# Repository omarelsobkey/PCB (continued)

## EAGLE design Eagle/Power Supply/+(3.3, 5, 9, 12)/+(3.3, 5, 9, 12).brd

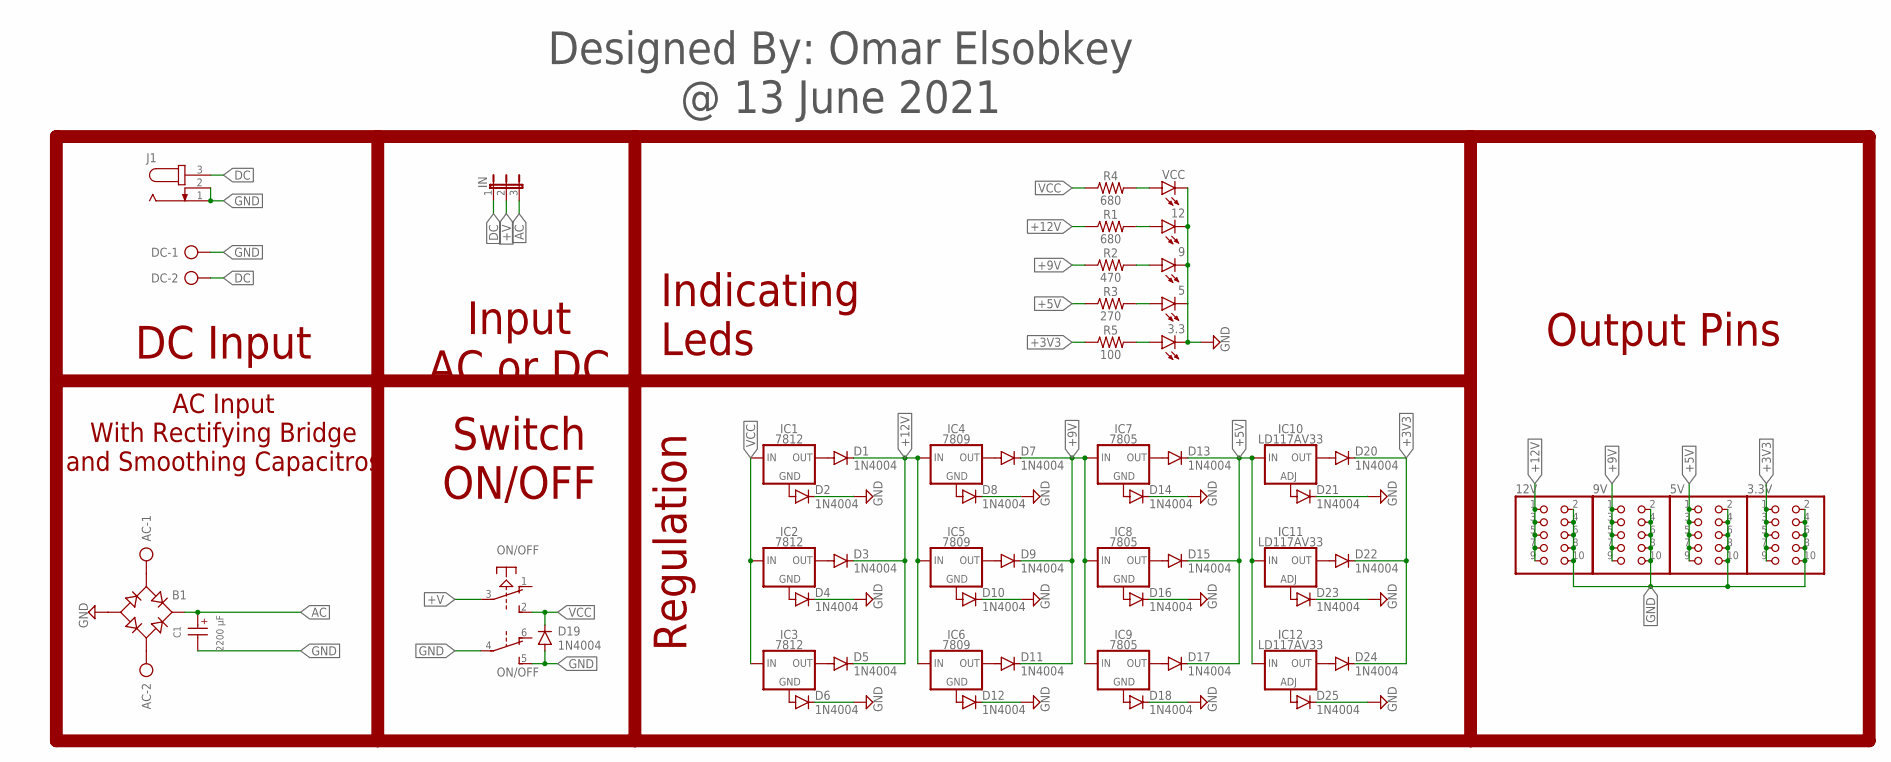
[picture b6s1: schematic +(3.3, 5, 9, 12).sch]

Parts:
3.3, 5, 9, 12: LED5MM
3.3V, 5V, 9V, 12V: PINHD-2X5; 2X05
AC: AK500/2-H
B1: RB1A
C1: 2200 µF; WCAP-ATG8_16X25(DXL)
D1, D2, D3, D4, D5, D6, D7, D8, D9, D10, D11, D12, D13, D14, D15, D16, D17, D18, D19, D20, D21, D22, D23, D24, D25: 1N4004; DO41-10
DC: AK500/2-H
IC1, IC2, IC3: 7812; 78XXS
IC4, IC5, IC6: 7809; 78XXS
IC7, IC8, IC9: 7805; 78XXS
IC10, IC11, IC12: LD117AV33; TO220L1
IN: JP2E; JP2
J1: JACK-PLUG0; SPC4077
ON/OFF: PVA2R
R1, R4: 680; AXIAL-0.3
R2: 470; AXIAL-0.3
R3: 270; AXIAL-0.3
R5: 100; AXIAL-0.3
VCC: LED5MM

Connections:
+3V3: 3.3V.1, 3.3V.3, 3.3V.5, 3.3V.7, 3.3V.9, D20.C, D22.C, D24.C, R5.P$1 (1)
+5V: 5V.1, 5V.3, 5V.5, 5V.7, 5V.9, D13.C, D15.C, D17.C, IC10.3 (IN), IC11.3 (IN), IC12.3 (IN), R3.P$1 (1)
+9V: 9V.1, 9V.3, 9V.5, 9V.7, 9V.9, D7.C, D9.C, D11.C, IC7.IN, IC8.IN, IC9.IN, R2.P$1 (1)
+12V: 12V.1, 12V.3, 12V.5, 12V.7, 12V.9, D1.C, D3.C, D5.C, IC4.IN, IC5.IN, IC6.IN, R1.P$1 (1)
+V: IN.2, ON/OFF.3
AC: B1.+, C1.1 (+), IN.3
DC: DC.2, IN.1, J1.3
GND: 3.3.K (C), 3.3V.2, 3.3V.4, 3.3V.6, 3.3V.8, 3.3V.10, 5.K (C), 5V.2, 5V.4, 5V.6, 5V.8, 5V.10, 9.K (C), 9V.2, 9V.4, 9V.6, 9V.8, 9V.10, 12.K (C), 12V.2, 12V.4, 12V.6, 12V.8, 12V.10, B1.-, C1.2 (-), D2.C, D4.C, D6.C, D8.C, D10.C, D12.C, D14.C, D16.C, D18.C, D19.A, D21.C, D23.C, D25.C, DC.1, J1.1, J1.2, ON/OFF.4, ON/OFF.5 (S), VCC.K (C)
unnamed: AC.1, B1.AC1
unnamed: AC.2, B1.AC2
unnamed: 3.3.A, R5.P$2 (2)
unnamed: R4.P$2 (2), VCC.A
unnamed: D21.A, IC10.1 (ADJ)
unnamed: D1.A, IC1.OUT
unnamed: D2.A, IC1.GND
unnamed: D3.A, IC2.OUT
unnamed: D4.A, IC2.GND
unnamed: D5.A, IC3.OUT
unnamed: D6.A, IC3.GND
unnamed: D7.A, IC4.OUT
unnamed: D8.A, IC4.GND
unnamed: D9.A, IC5.OUT
unnamed: D10.A, IC5.GND
unnamed: D11.A, IC6.OUT
unnamed: D12.A, IC6.GND
unnamed: D13.A, IC7.OUT
unnamed: D14.A, IC7.GND
unnamed: D15.A, IC8.OUT
unnamed: D16.A, IC8.GND
unnamed: D17.A, IC9.OUT
unnamed: D18.A, IC9.GND
unnamed: 12.A, R1.P$2 (2)
unnamed: 9.A, R2.P$2 (2)
unnamed: 5.A, R3.P$2 (2)
unnamed: D22.A, IC11.2 (OUT)
unnamed: D23.A, IC11.1 (ADJ)
unnamed: D24.A, IC12.2 (OUT)
unnamed: D25.A, IC12.1 (ADJ)
unnamed: D20.A, IC10.2 (OUT)
VCC: D19.C, IC1.IN, IC2.IN, IC3.IN, ON/OFF.2 (S), R4.P$1 (1)

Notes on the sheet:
Regulation
Indicating Leds
Input AC or DC
Switch ON/OFF
AC Input With Rectifying Bridge and Smoothing Capacitros
DC Input
Output Pins
Designed By: Omar Elsobkey @ 13 June 2021

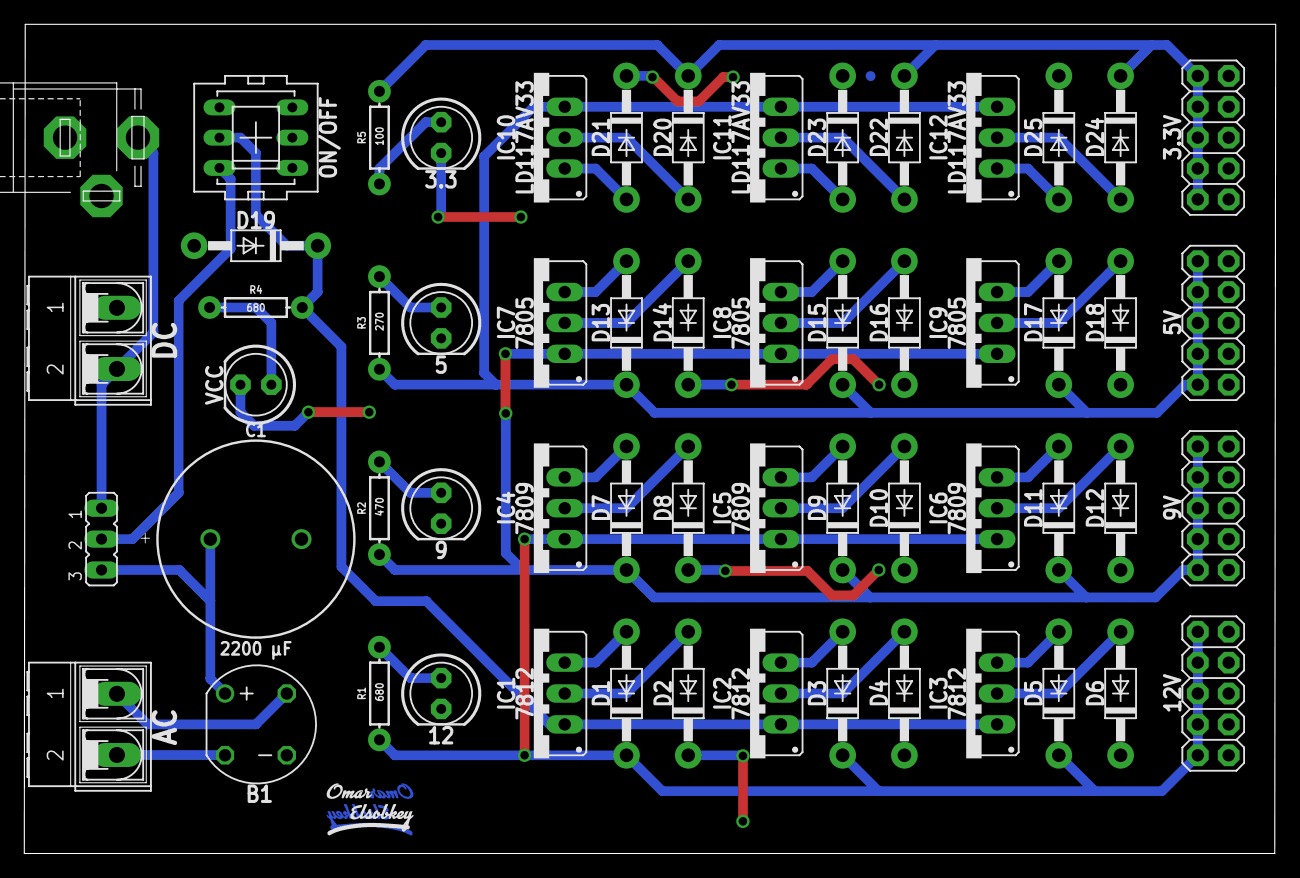
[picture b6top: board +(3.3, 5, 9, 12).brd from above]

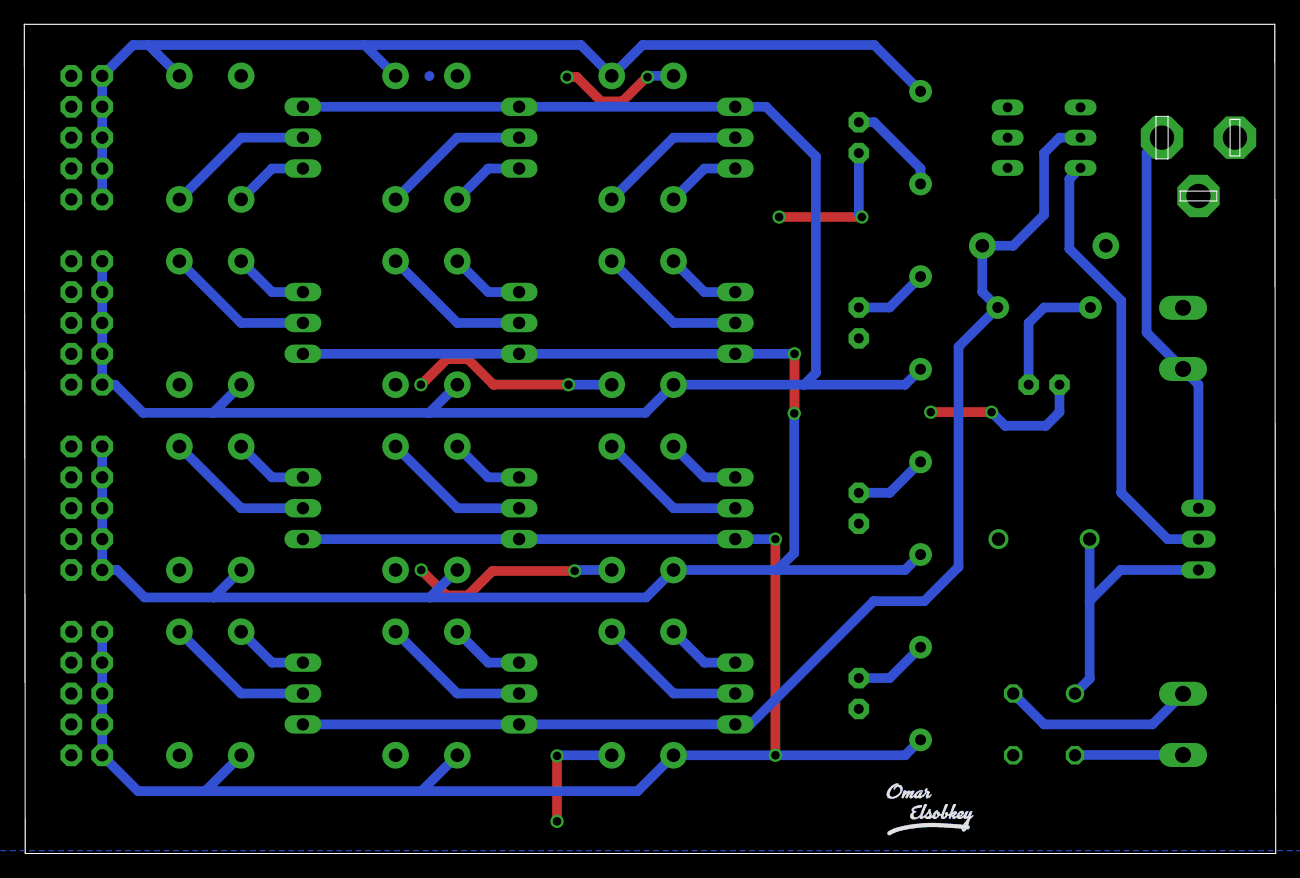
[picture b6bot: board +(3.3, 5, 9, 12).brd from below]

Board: 2 copper layers, 102.9 x 68.2 mm, 61 parts (2 on the bottom side), 40 nets.

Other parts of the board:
U$1: OMAR_ELSOBKEY_X0.5_T
U$2, U$3: OMAR_ELSOBKEY_X0.5_TN

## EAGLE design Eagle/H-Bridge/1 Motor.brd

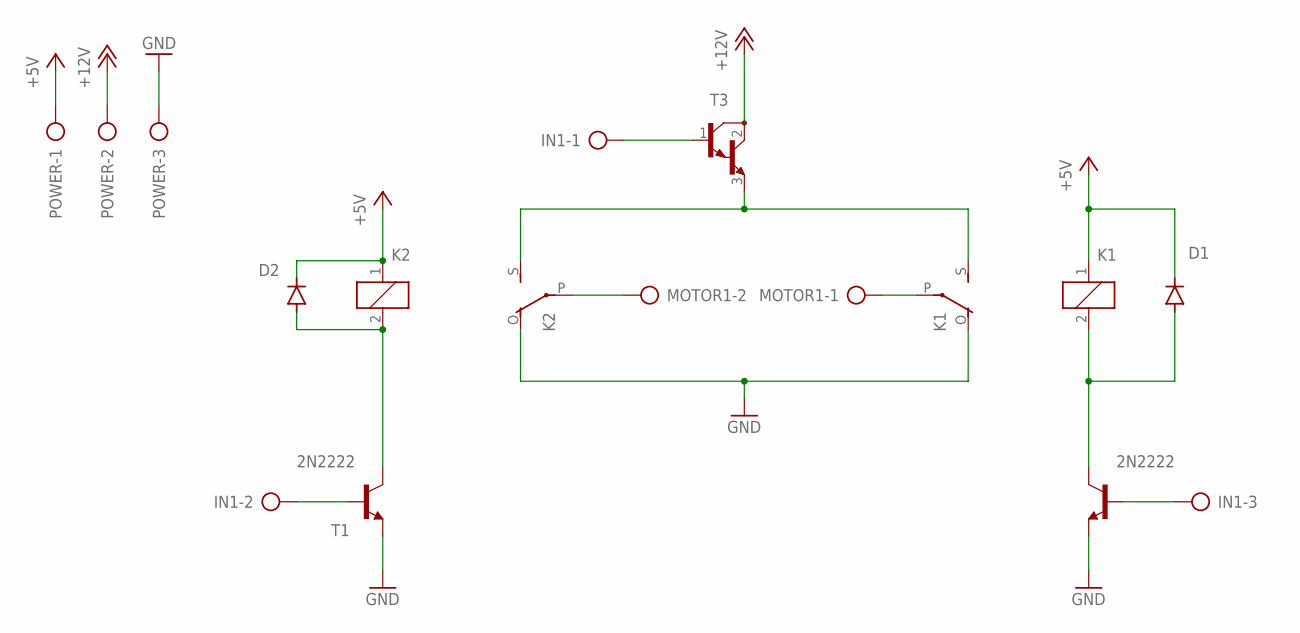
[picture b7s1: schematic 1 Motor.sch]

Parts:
D1, D2: 1N4004; DO41-10
IN1: AK300/3
K1, K2: ZF112
MOTOR1: AK300/2
POWER: AK300/3
T1, T2: 2N2222; TO92-EBC
T3: TIP122; TO220

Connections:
+5V: D1.C, D2.C, K1.1, K2.1, POWER.1
+12V: POWER.2, T3.2 (C)
EN: IN1.1, T3.1 (B)
GND: K1.O, K2.O, POWER.3, T1.E, T2.E
IN1: IN1.2, T1.B
IN2: IN1.3, T2.B
unnamed: K2.P, MOTOR1.2
unnamed: D1.A, K1.2, T2.C
unnamed: K1.P, MOTOR1.1
unnamed: D2.A, K2.2, T1.C
NO: K1.S, K2.S, T3.3 (E)

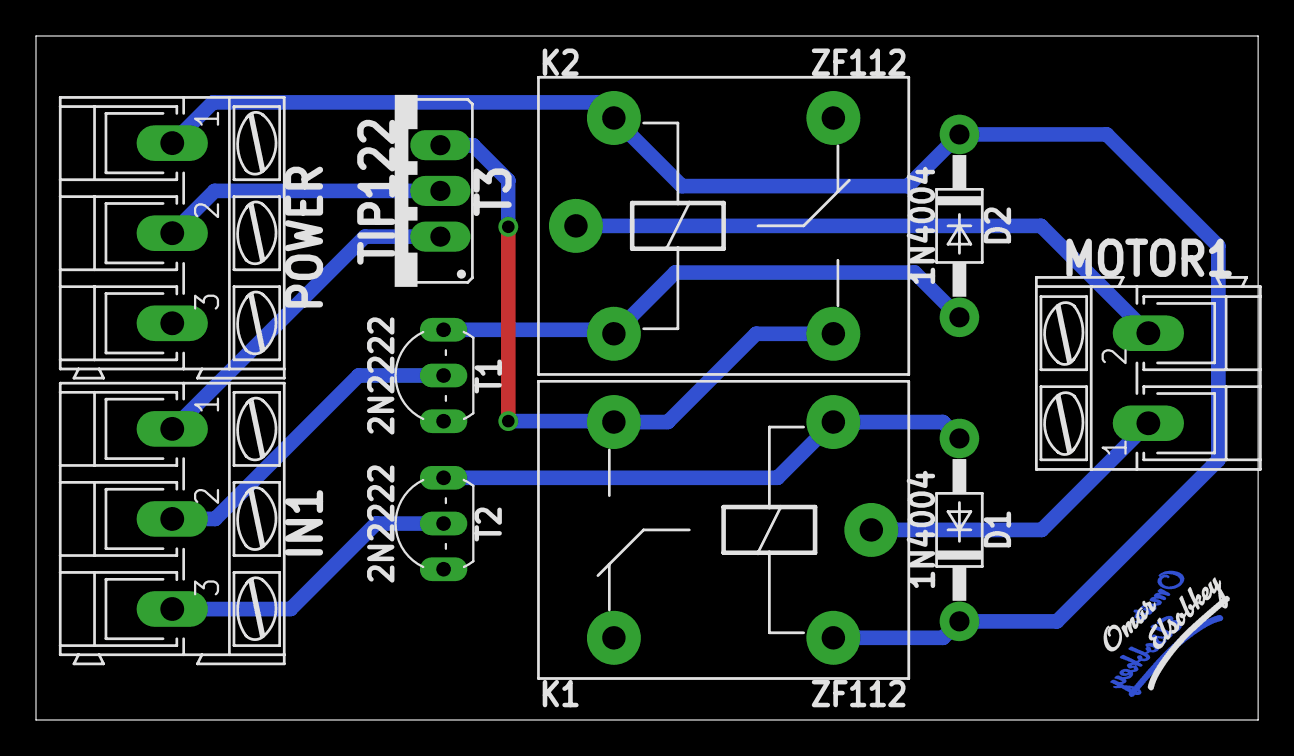
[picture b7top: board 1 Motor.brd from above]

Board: 2 copper layers, 67.9 x 38.0 mm, 12 parts (1 on the bottom side), 11 nets.

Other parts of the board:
U$1: OMAR_ELSOBKEY_X0.5_T
U$2: OMAR_ELSOBKEY_X0.5_TN

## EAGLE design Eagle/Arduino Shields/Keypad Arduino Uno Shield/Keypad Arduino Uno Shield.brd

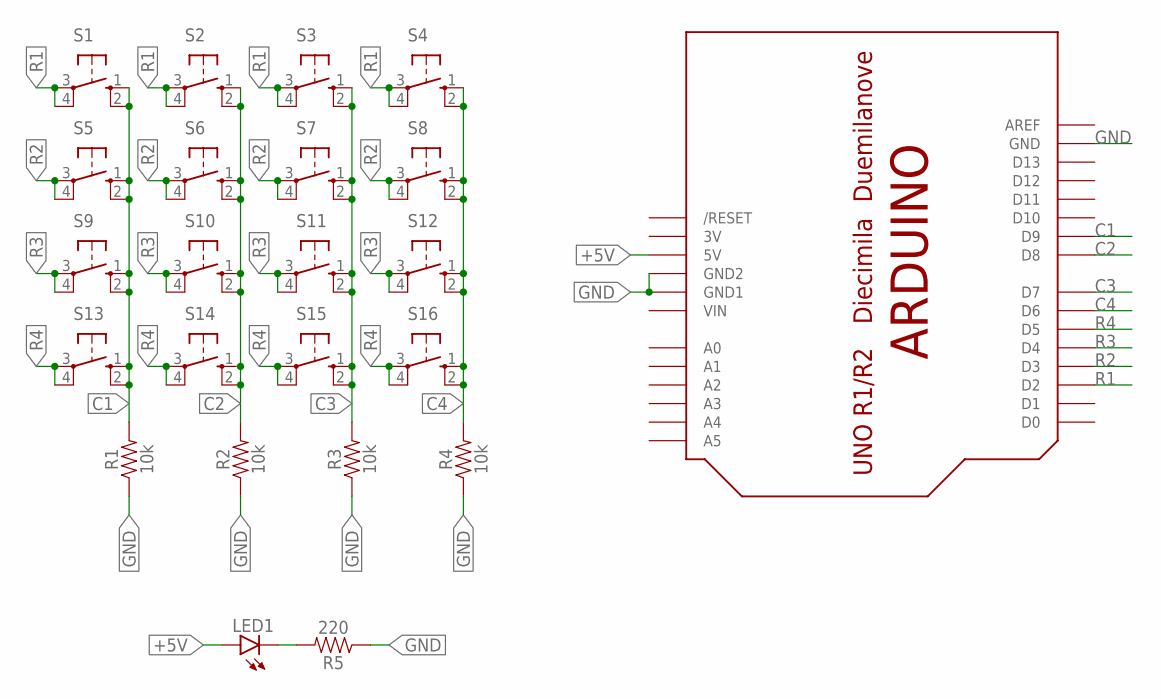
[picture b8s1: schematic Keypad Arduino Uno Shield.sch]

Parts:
LED1: LEDSML0805; SML0805
R1, R2, R3, R4: 10k; 1206
R5: 220; 1206
S1, S2, S3, S4, S5, S6, S7, S8, S9, S10, S11, S12, S13, S14, S15, S16: 10-XX; B3F-10XX
U$1: ARDUINOUNO; ARDUINO

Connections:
3V: U$1.3V
+5V: LED1.A, U$1.5V
C1: R1.2, S1.1 (S), S1.2 (S1), S5.1 (S), S5.2 (S1), S9.1 (S), S9.2 (S1), S13.1 (S), S13.2 (S1), U$1.D9
C2: R2.2, S2.1 (S), S2.2 (S1), S6.1 (S), S6.2 (S1), S10.1 (S), S10.2 (S1), S14.1 (S), S14.2 (S1), U$1.D8
C3: R3.2, S3.1 (S), S3.2 (S1), S7.1 (S), S7.2 (S1), S11.1 (S), S11.2 (S1), S15.1 (S), S15.2 (S1), U$1.D7
C4: R4.2, S4.1 (S), S4.2 (S1), S8.1 (S), S8.2 (S1), S12.1 (S), S12.2 (S1), S16.1 (S), S16.2 (S1), U$1.D6
GND: R1.1, R2.1, R3.1, R4.1, R5.1, U$1.GND, U$1.GND1, U$1.GND2
unnamed: LED1.C, R5.2
R1: S1.3, S1.4 (P1), S2.3, S2.4 (P1), S3.3, S3.4 (P1), S4.3, S4.4 (P1), U$1.D2
R2: S5.3, S5.4 (P1), S6.3, S6.4 (P1), S7.3, S7.4 (P1), S8.3, S8.4 (P1), U$1.D3
R3: S9.3, S9.4 (P1), S10.3, S10.4 (P1), S11.3, S11.4 (P1), S12.3, S12.4 (P1), U$1.D4
R4: S13.3, S13.4 (P1), S14.3, S14.4 (P1), S15.3, S15.4 (P1), S16.3, S16.4 (P1), U$1.D5
VIN: U$1.VIN

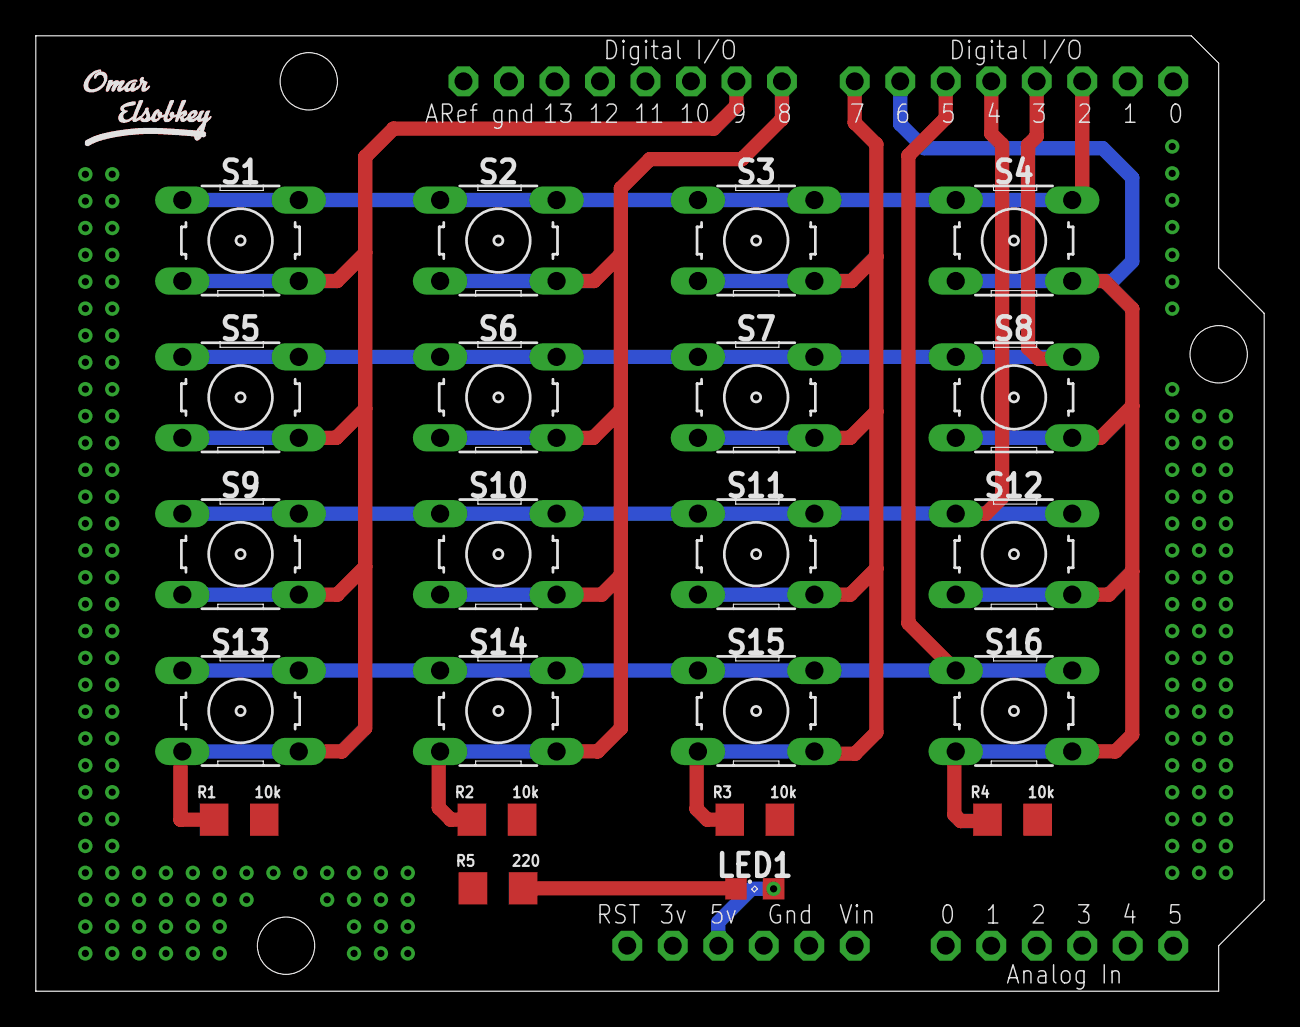
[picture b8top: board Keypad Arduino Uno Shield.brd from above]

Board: 2 copper layers, 68.6 x 53.3 mm, 24 parts (0 on the bottom side), 11 nets.

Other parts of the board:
U$2: OMAR_ELSOBKEY_X0.5

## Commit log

2021-05-24 uploading all old design as a starting point
2021-05-25 re-arrange items and use the right package of the relay.
2021-06-13 Modify the footprints of some of the components and modify the drill size of the vias to be more compatable with being made at home
2021-06-21 Finish routing.
2021-06-21 new project. bi-direction logic level converter.
2021-06-26 in this version i replaced the transistors with optocoupler and corrected the connection of the voltage regulator.
2021-06-30 Add old files.
2021-06-30 remove unnecessary file.
2021-06-30 Add tutorial design files and modify the 3d of the power supply design.
2021-08-03 Upload modified and old files.
